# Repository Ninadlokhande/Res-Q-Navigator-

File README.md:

# Res-Q-Navigator-

## Overview
An intelligent rescue navigation robot designed to detect fire and smoke, avoid obstacles, find path, and respond to emergencies with automated water deployment and wireless communication using Bluetooth. Powered by Arduino microcontroller , DHT11, MQ2, Ultrasonic sensors, and an L293D motor driver

## Features
- Fire detection using DHT11 temperature and MQ2 smoke sensors  
- Obstacle avoidance with ultrasonic sensors  
- Automatic water pump activation to extinguish the fire  
- Controlled via Arduino microcontroller with L298N motor driver  
- Real-time response to environmental hazards

## Components Used
- Arduino Uno  
- DHT11 Temperature and Humidity Sensor  
- MQ2 Smoke Sensor  
- Ultrasonic Sensor (HC-SR04)  
- L298N Motor Driver  
- Water Pump  
- Jumper wires, breadboard, and chassis components

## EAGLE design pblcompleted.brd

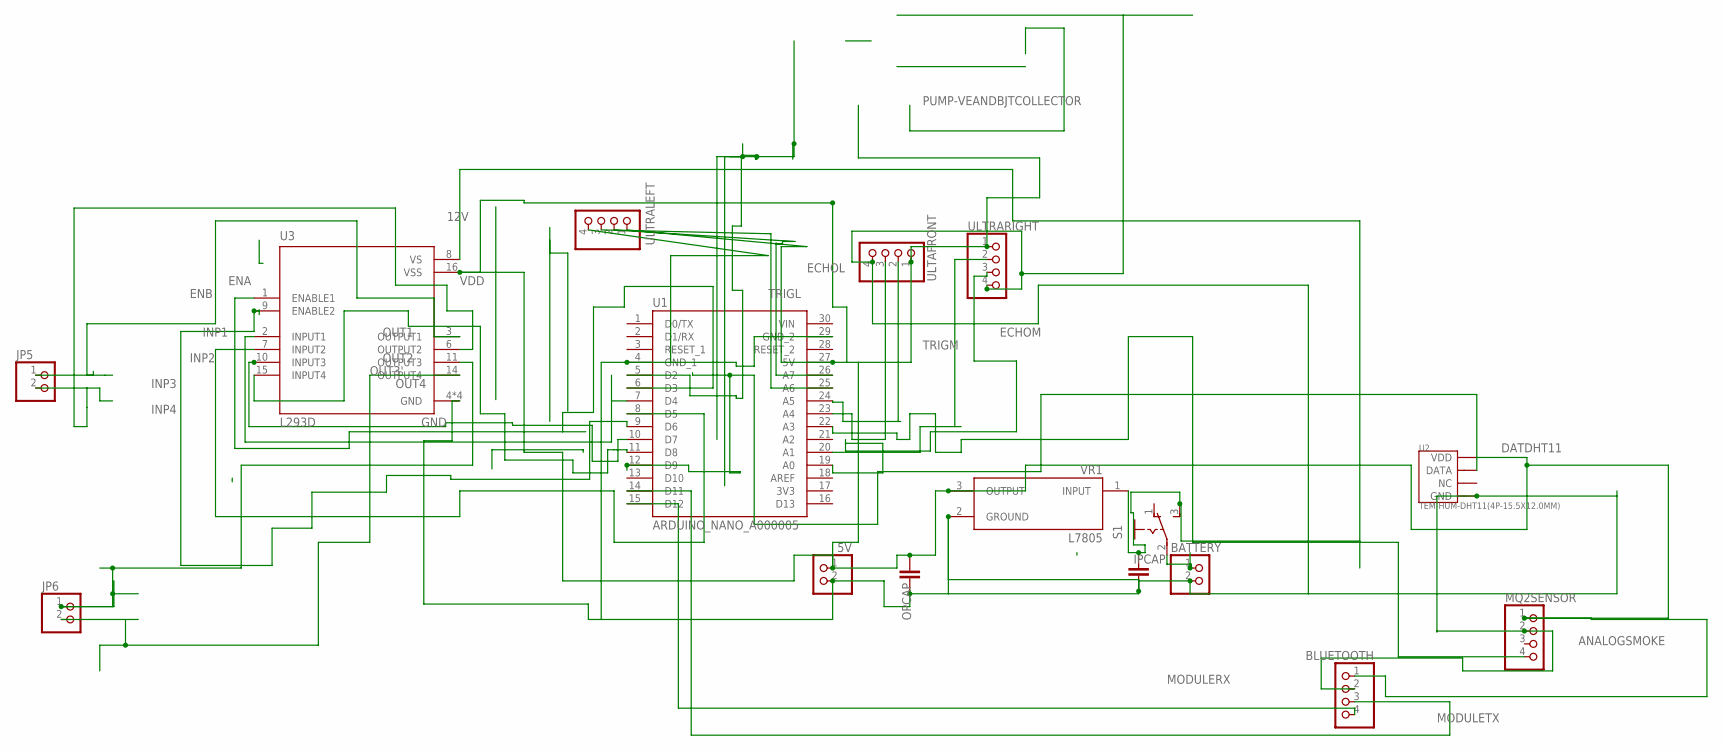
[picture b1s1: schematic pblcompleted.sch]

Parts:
5V: PINHD-1X2; 1X02
BATTERY: PINHD-1X2; 1X02
BLUETOOTH: PINHD-1X4; 1X04
IPCAP: C2,5-3; C2.5-3
JP5, JP6: PINHD-1X2; 1X02
MQ2SENSOR: PINHD-1X4; 1X04
OPCAP: C2,5-3; C2.5-3
S1: 255SB
U1: ARDUINO_NANO_A000005; MODULE_ARDUINO_NANO_A000005
U2: TEM-HUM-DHT11(4P-15.5X12.0MM); SNR4-2.54-15.5X12.0X5.5MM
U3: L293D; DIP880W50P254L2000H510Q16
ULTAFRONT: PINHD-1X4; 1X04
ULTRALEFT: PINHD-1X4; 1X04
ULTRARIGHT: PINHD-1X4; 1X04
VR1: L7805; TO255P1020X450X2000-3

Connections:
3V3: U1.17 (3V3)
12V: IPCAP.1, S1.3 (S), U3.8 (VS), VR1.1 (INPUT)
ANALOGSMOKE: MQ2SENSOR.4, U1.22 (A3)
DATDHT11: U1.12 (D9), U2.2 (DATA)
ECHOL: U1.25 (A6), ULTRALEFT.3
ECHOM: U1.23 (A4), ULTAFRONT.3
ECHOR: U1.19 (A0), ULTRARIGHT.3
ENA: U1.6 (D3), U3.1 (ENABLE1)
ENB: U1.9 (D6), U3.9 (ENABLE2)
GND: 5V.2, BATTERY.2, BLUETOOTH.2, IPCAP.2, MQ2SENSOR.2, OPCAP.1, U1.4 (GND_1), U1.29 (GND_2), U2.4 (GND), U3.4 (GND), U3.5 (GND), U3.12 (GND), U3.13 (GND), ULTAFRONT.4, ULTRALEFT.4, ULTRARIGHT.4, VR1.2 (GROUND)
INP1: U1.7 (D4), U3.2 (INPUT1)
INP2: U1.8 (D5), U3.7 (INPUT2)
INP3: U1.10 (D7), U3.10 (INPUT3)
INP4: U1.11 (D8), U3.15 (INPUT4)
MODULERX: BLUETOOTH.4, U1.15 (D12)
MODULETX: BLUETOOTH.3, U1.14 (D11)
unnamed: BATTERY.1, S1.2
OUT1: JP5.1, U3.3 (OUTPUT1)
OUT2: JP5.2, U3.6 (OUTPUT2)
OUT3': JP6.1, U3.11 (OUTPUT3)
OUT4: JP6.2, U3.14 (OUTPUT4)
TRIGL: U1.26 (A7), ULTRALEFT.2
TRIGM: U1.24 (A5), ULTAFRONT.2
TRIGR: U1.20 (A1), ULTRARIGHT.2
VDD: 5V.1, BLUETOOTH.1, MQ2SENSOR.1, OPCAP.2, U1.27 (5V), U2.1 (VDD), U3.16 (VSS), ULTAFRONT.1, ULTRALEFT.1, ULTRARIGHT.1, VR1.3 (OUTPUT)
VIN: U1.30 (VIN)

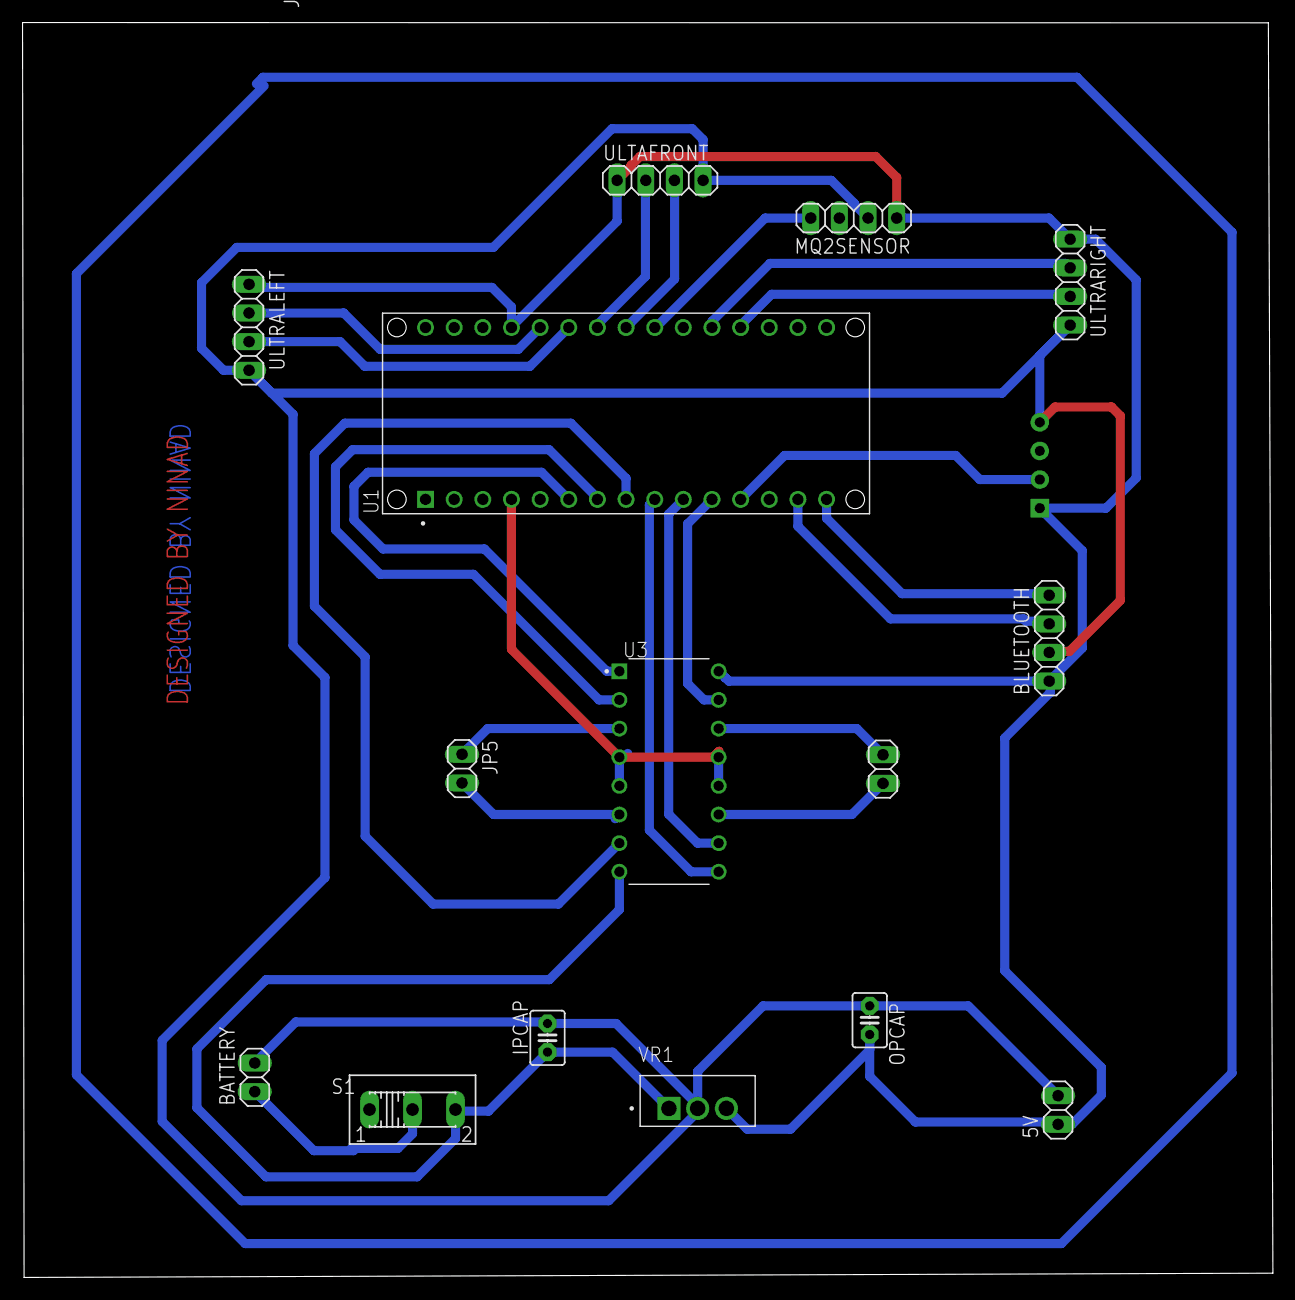
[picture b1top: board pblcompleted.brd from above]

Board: 2 copper layers, 110.9 x 111.3 mm, 16 parts (1 on the bottom side), 24 nets.

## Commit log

2025-05-16 Create overview and use and advantages and properties
2025-07-07 Add files via upload
    🛠️ PCB Design – ResQ Navigator
    Designed this custom PCB using Autodesk EAGLE for the ResQ Navigator, a robotics project focused on fire and obstacle detection in rescue operations.
    The board integrates:
    🔥 DHT11 & MQ2 for fire and smoke sensing
    📡 Ultrasonic sensors for obstacle avoidance
    🧠 Microcontroller and L298N motor driver for motion control
2025-07-07 Add files via upload
    code for working of robot
